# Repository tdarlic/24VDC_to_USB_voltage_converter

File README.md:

# 24VDC to USB voltage converter
Kicad project

Converts voltage from 9 to 24 volts from the boat batteries to 5V USB using Texas Instruments TPS54308

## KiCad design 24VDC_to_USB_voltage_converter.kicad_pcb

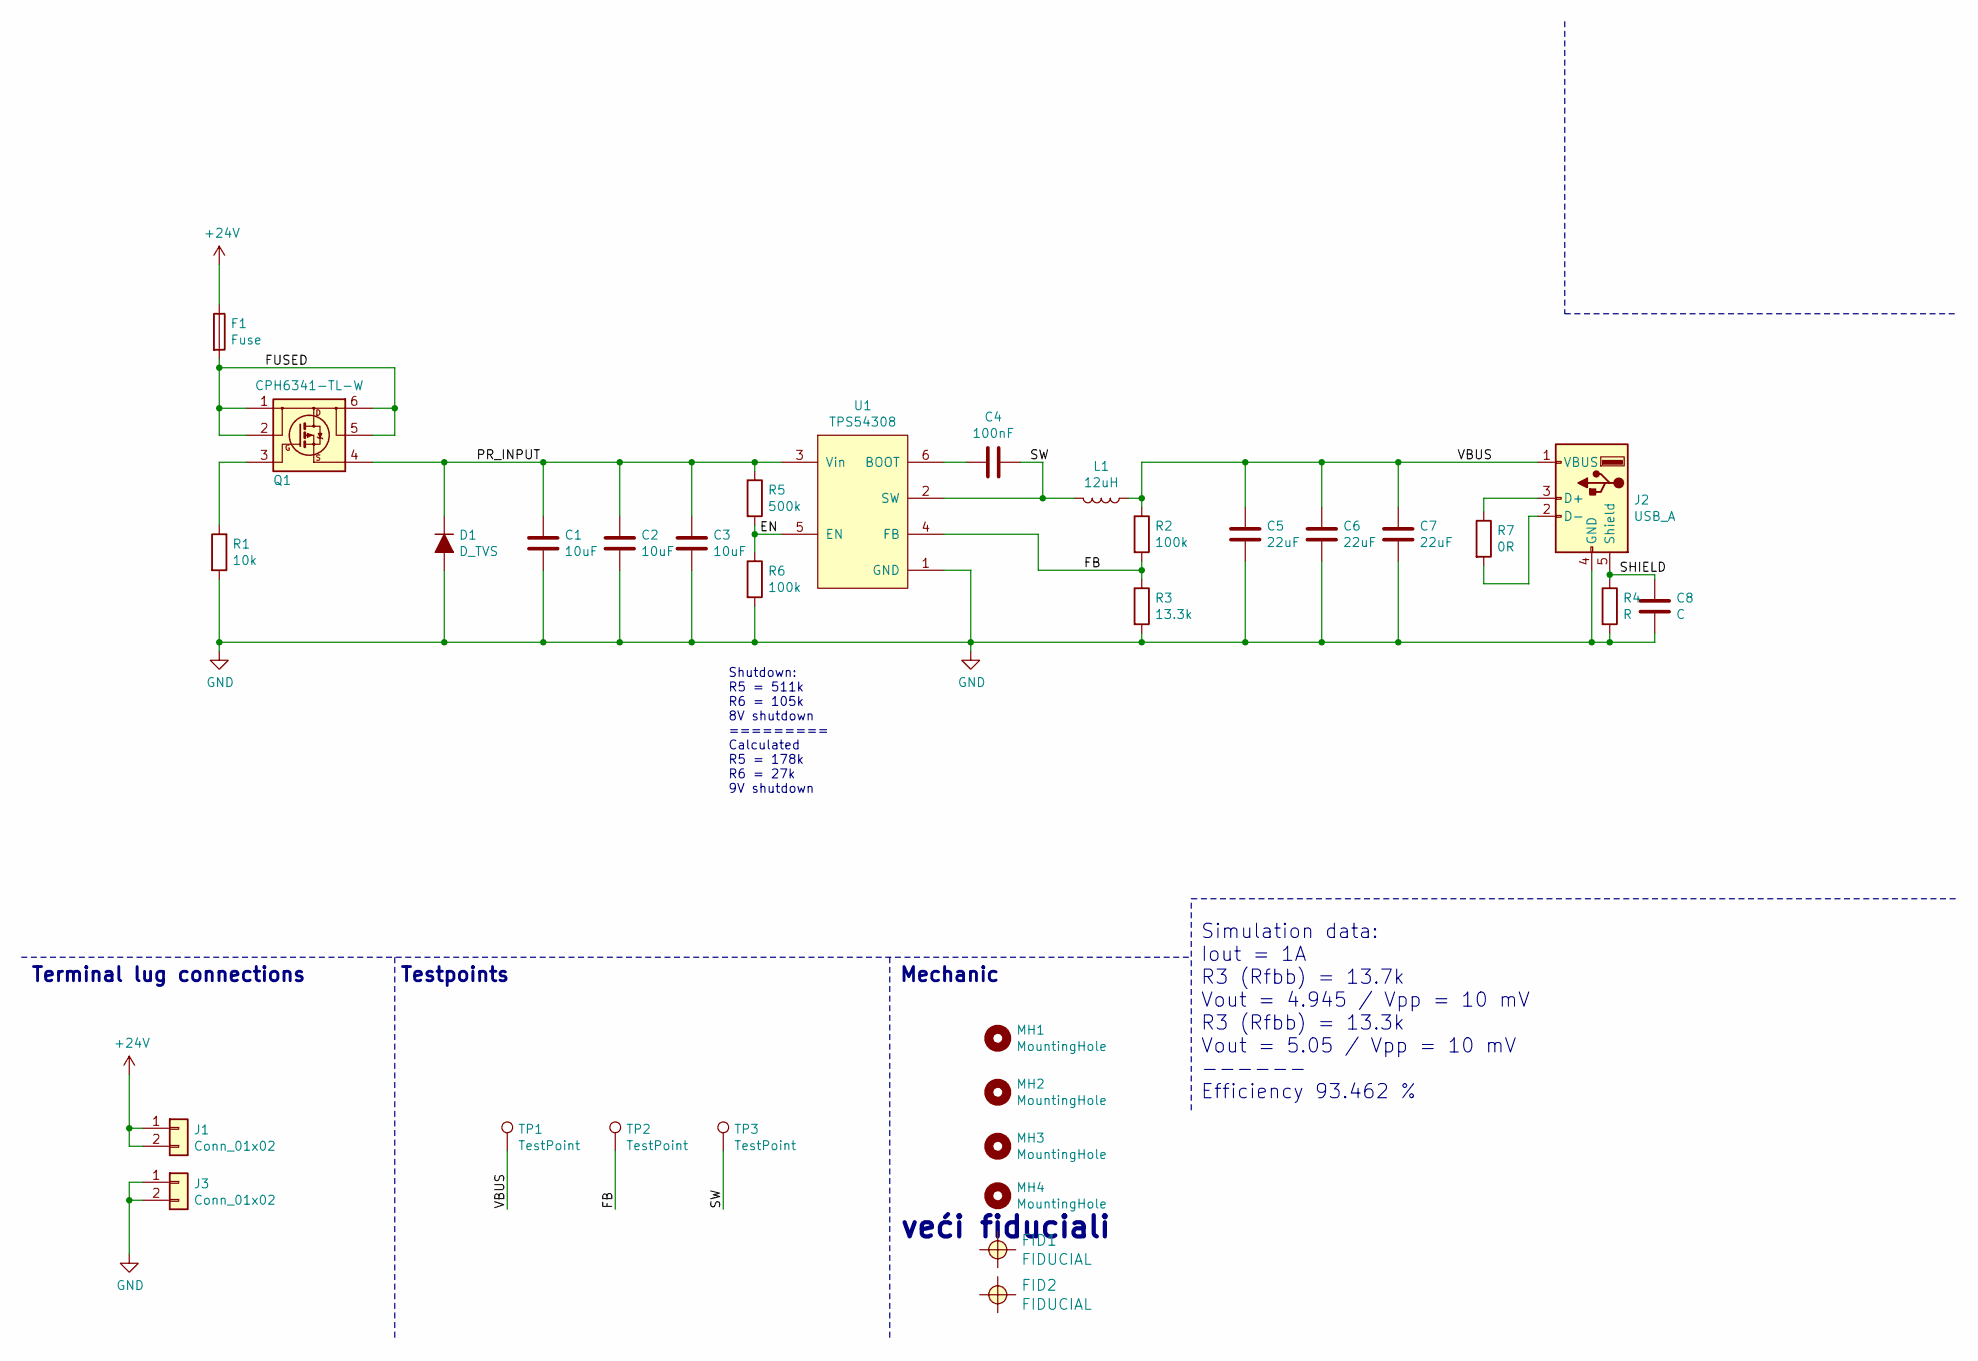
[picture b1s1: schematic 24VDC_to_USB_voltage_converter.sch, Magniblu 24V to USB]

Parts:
C1, C2, C3: 10uF; C_1206_3216Metric; Mouser code 81-GRT31CR61H106ME1L
C4: 100nF; C_0603_1608Metric; Mouser code 603-CC603KRX7R9BB104
C5, C6, C7: 22uF; R_0805_2012Metric; Mouser code 81-GRM21BR61E226ME4K
C8: C; C_0603_1608Metric
D1: D_TVS; D-FLAT; Mouser code 621-P4SMAJ30ADF-13
F1: Fuse; Fuse_2410_(6125_metric); Mouser code 530-0679L1500-05
FID1, FID2: FIDUCIAL
J1, J3: Conn_01x02; TE FASTON 250 TAB 928814-1; Mouser code 571-928814-1
J2: USB_A; BEL-USBA-SS-52100-001; Mouser code 530-SS-52100-001
L1: 12uH; L_Wuerth_WE-PD2-Typ-L; Mouser code 652-SDE0805A-120M
MH1, MH2, MH3, MH4: MountingHole; MountingHole_2.5mm
Q1: CPH6341-TL-W; SOT-23-6_Handsoldering; Mouser code 863-CPH6341-TL-W
R1: 10k; R_0603_1608Metric
R2: 100k; R_0603_1608Metric; Mouser code 755-SFR03EZPF1003
R3: 13.3k; R_0603_1608Metric; Mouser code 603-AC0603FR-0713K3L
R4: R; R_0603_1608Metric
R5: 500k; R_0603_1608Metric
R6: 100k; R_0603_1608Metric
R7: 0R; R_0603_1608Metric
TP1, TP2, TP3: TestPoint; TestPoint_Pad_D1.5mm
U1: TPS54308; SOT-23-6_Handsoldering; Mouser code 595-TPS54308DDCR

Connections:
+24V: F1.1, J1.1, J1.2
/EN: R5.2, R6.1, U1.5 (EN)
/FB: R2.2, R3.1, TP2.1, U1.4 (FB)
/FUSED: F1.2, Q1.1 (D), Q1.2 (D), Q1.5 (D), Q1.6 (D)
/PR_INPUT: C1.1, C2.1, C3.1, D1.1 (K), Q1.4 (S), R5.1, U1.3 (Vin)
/SHIELD: C8.1, J2.5 (Shield), R4.1
/SW: C4.1, L1.2, TP3.1, U1.2 (SW)
/VBUS: C5.1, C6.1, C7.1, J2.1 (VBUS), L1.1, R2.1, TP1.1
GND: C1.2, C2.2, C3.2, C5.2, C6.2, C7.2, C8.2, D1.2 (A), J2.4 (GND), J3.1, J3.2, R1.2, R3.2, R4.2, R6.2, U1.1 (GND)
unnamed: C4.2, U1.6 (BOOT)
unnamed: J2.2 (D-), R7.2
unnamed: J2.3 (D+), R7.1
unnamed: Q1.3 (G), R1.1

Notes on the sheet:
Terminal lug connections
Simulation data: Iout = 1A R3 (Rfbb) = 13.7k Vout = 4.945 / Vpp = 10 mV R3 (Rfbb) = 13.3k Vout = 5.05 / Vpp = 10 mV ------ Efficiency 93.462 %
Testpoints
Shutdown: R5 = 511k R6 = 105k 8V shutdown ========= Calculated R5 = 178k R6 = 27k 9V shutdown
Mechanic
veći fiduciali

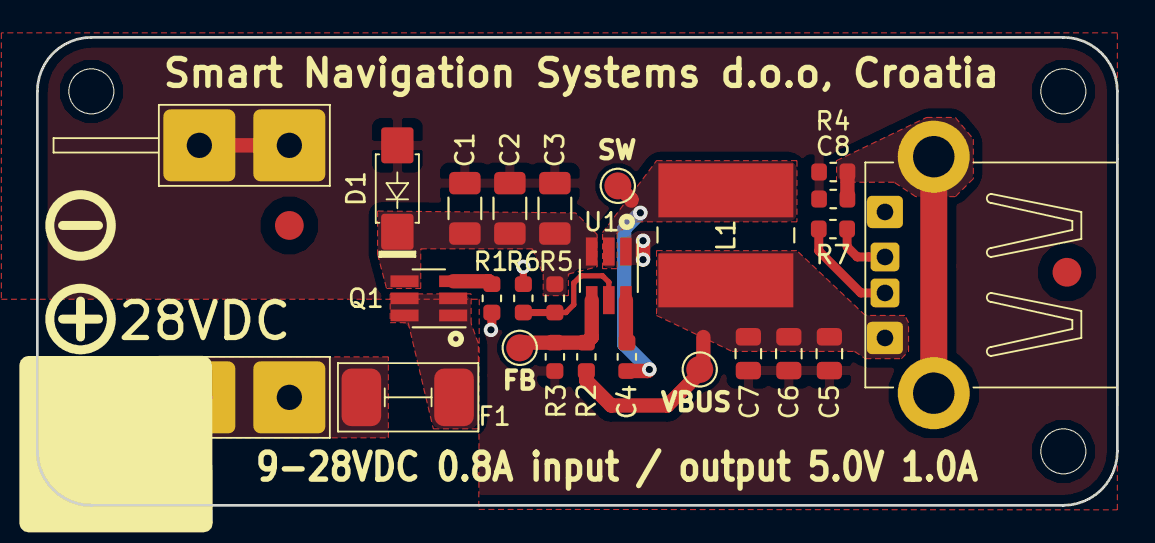
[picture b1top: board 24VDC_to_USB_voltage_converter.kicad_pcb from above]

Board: 2 copper layers, 60.0 x 26.0 mm, 32 parts (0 on the bottom side), 13 nets.

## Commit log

2019-02-21 Updating readme
2019-02-21 Adding PDF schematic
2019-02-28 Adding final changes and exporting Gerbers
2019-03-07 Finishing the board and creating gerbers for ordering
2019-03-07 Adding short resistor between d+ and d-, small changes in PCB
2019-03-07 Adding PDF file, removing comments from schematic, adding scope image in schematic
2019-03-08 Adding noise characteristic to schematic and rearranging some items in schematic
2019-03-25 Adding one comment to schematic
